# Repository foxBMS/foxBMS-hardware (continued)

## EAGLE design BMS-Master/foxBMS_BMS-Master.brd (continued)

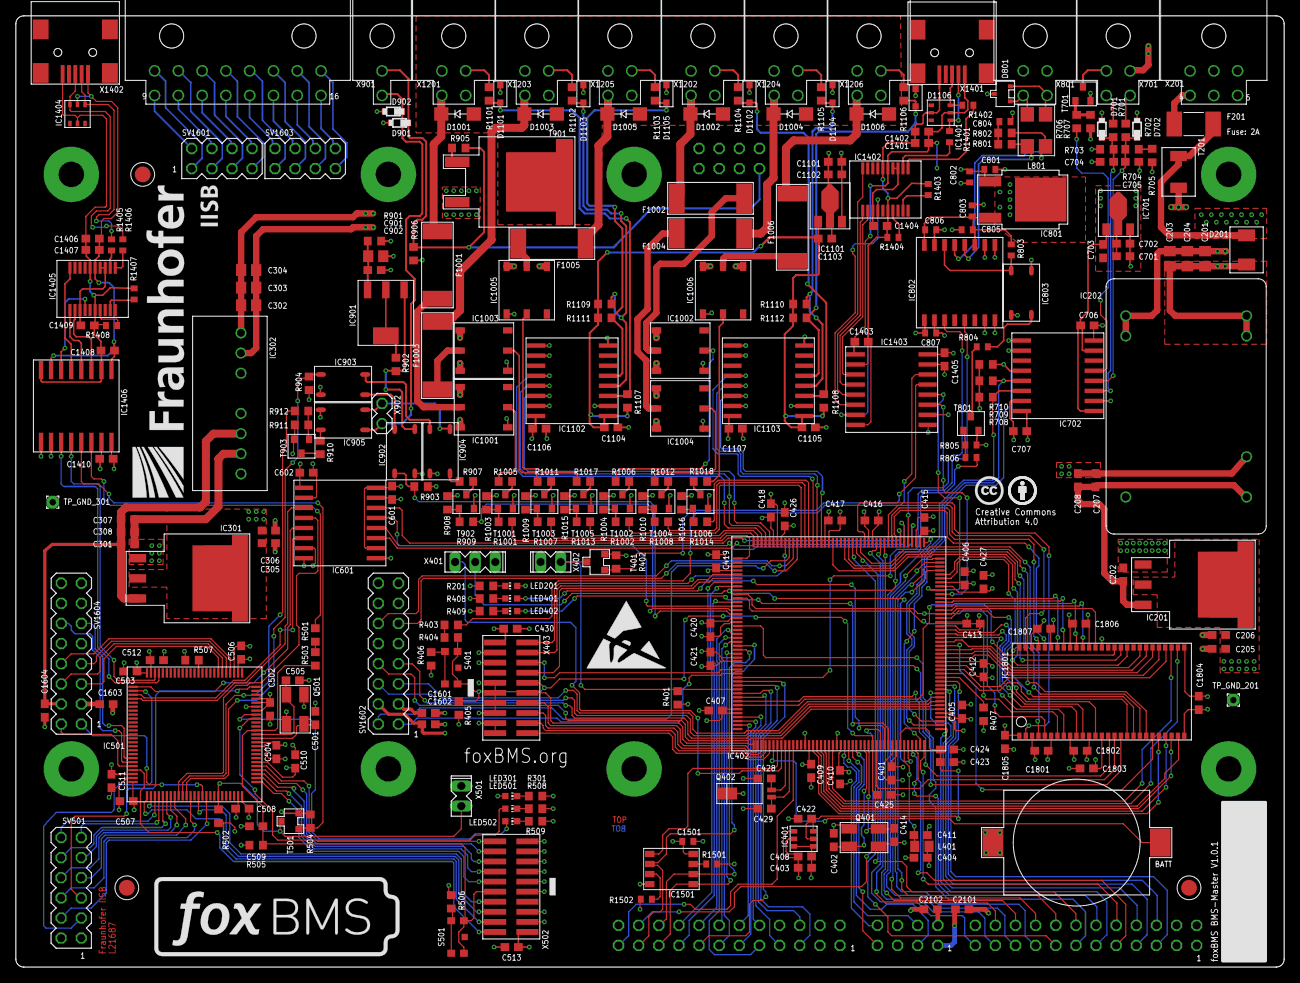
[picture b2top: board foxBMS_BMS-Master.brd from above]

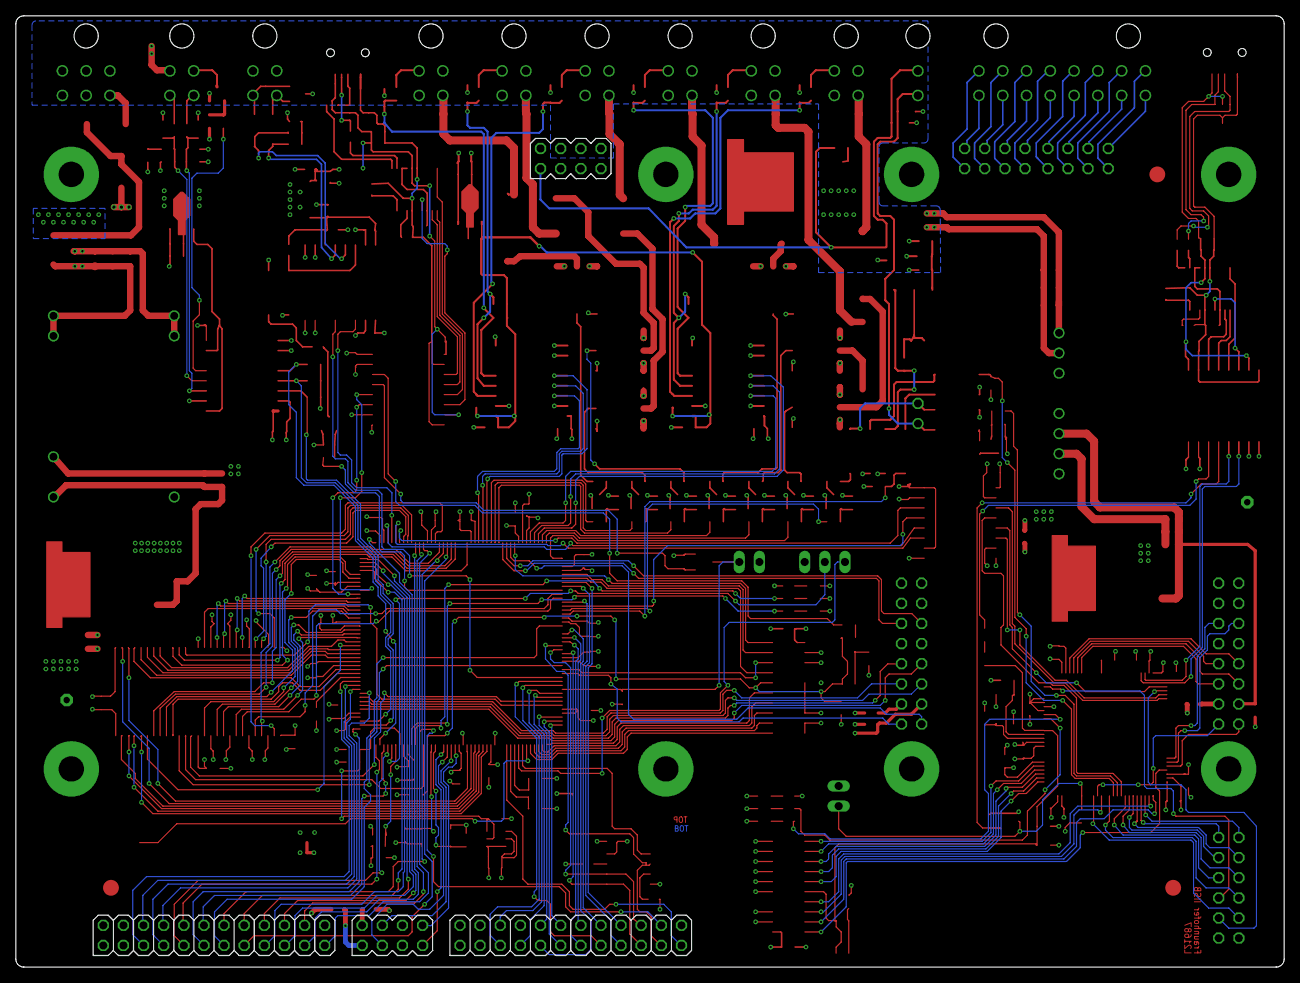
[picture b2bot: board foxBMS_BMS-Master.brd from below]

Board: 4 copper layers, 160.0 x 120.0 mm, 318 parts (4 on the bottom side), 331 nets.

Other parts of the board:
U$1, U$3, U$4: FIDUCIAL_1MM
U$2: ESD_10.00

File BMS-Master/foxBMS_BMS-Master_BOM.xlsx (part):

| Pos | Populate | Qty | Value | Device | Package | Parts | Description | Farnell | Digikey | Mouser
Resistor
 | 1 | yes | 9 | 0 | R-EU_R0603 | R0603 | R403 R406 R501 R506 R705 R1403 R1404 R1407 R1408 | RESISTOR, European symbol | 2059527
 | 2 | yes | 2 | 1.5k | R-EU_R0603 | R0603 | R701 R702 | RESISTOR, European symbol | 2303156
 | 3 | yes | 12 | 10 | R-EU_R0603 | R0603 | R706 R901 R905 R909 R912 R1001 R1002 R1007 R1008 R1013 R1014 R806 | RESISTOR, European symbol | 2302958
 | 4 | yes | 32 | 10k | R-EU_R0603 | R0603 | R401 R402 R405 R407 R502 R504 R505 R507 R707 R708 R709 R710 R903 R904 R908 R911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 | RESISTOR, European symbol | 2303192
 | 5 | yes | 1 | 120 | R-EU_R0603 | R0603 | R902 | RESISTOR, European symbol | 2303067
 | 6 | yes | 6 | 130 | R-EU_R0603 | R0603 | R201 R301 R408 R409 R508 R509 | RESISTOR, European symbol | 2059288
 | 7 | yes | 8 | 430 | R-EU_R0603 | R0603 | R907 R910 R1005 R1006 R1011 R1012 R1017 R1018 R804 | RESISTOR, European symbol | 2145386
 | 8 | yes | 1 | 330 | R-EU_R0603 | R0603 | R906 | RESISTOR, European symbol | 2145370
 | 9 | yes | 4 | 27 | R-EU_R0603 | R0603 | R1401 R1402 R1405 R1406 | RESISTOR, European symbol | 2145363
 | 10 | yes | 6 | 47 | R-EU_R0603 | R0603 | R1101 R1102 R1103 R1104 R1105 R1106 | RESISTOR, European symbol | 2145397
 | 11 | yes | 2 | 62 | R-EU_R0603 | R0603 | R801 R802 | RESISTOR, European symbol | 2303039
 | 12 | yes | 4 | 680 | R-EU_R0603 | R0603 | R404 R503 R703 R704 | RESISTOR, European symbol | 2303131
Capacitor
 | 13 | yes | 74 | 100n | C-EUC0603 | C0603 | C202 C206 C208 C301 C306 C308 C401 C404 C405 C406 C407 C408 C409 C410 C411 C412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 | CAPACITOR, European symbol | 1828890
 | 14 | yes | 4 | 100n 50V | C-EUC0604 | C0603 | C702 C802 C902 C1102 | CAPACITOR, European symbol | 2346967
 | 15 | yes | 8 | 18p | C-EUC0605 | C0603 | C402 C414 C428 C429 C501 C505 C704 C705 | CAPACITOR, European symbol | 2070403
 | 16 | yes | 6 | 1µ | C-EUC0606 | C0603 | C205 C207 C305 C307 C403 C423 | CAPACITOR, European symbol | 1907343
 | 17 | yes | 3 | 1µ 35V | C-EUC0607 | C0603 | C701 C801 C1101 | CAPACITOR, European symbol | 2346909
 | 18 | yes | 4 | 2.2µ | C-EUC0608 | C0603 | C426 C427 C511 C512 | CAPACITOR, European symbol | 2346961
 | 19 | yes | 7 | 2.2µ 50V | C-EUC0609 | C0805 | C201 C203 C204 C302 C303 C304 C901 | CAPACITOR, European symbol | 2346945
 | 20 | yes | 2 | 4.7µ | C-EUC0610 | C0603 | C1401 C1406 | CAPACITOR, European symbol | 2362098
L
 | 21 | yes | 1 |  | L0805 | 0805 | L401 |  | 2443249
 | 22 | yes | 1 |  | B82789N | B82789N | L801 |  |  |  | 871-B82789C513N2
LED
 | 23 | yes | 2 | Green | LEDCHIP-LED0603 | CHIP-LED0603 | LED402 LED502 | LED | 2099223
 | 24 | yes | 2 | Red | LEDCHIP-LED0603 | CHIP-LED0603 | LED401 LED501 | LED | 2099221
 | 25 | yes | 2 | Orange | LEDCHIP-LED0603 | CHIP-LED0603 | LED201 LED301 | LED | 2099222
XTAL
 | 26 | yes | 2 | 7B-8.000MAAJ-T | 7B-8.000MAAJ-T | MJ | Q401 Q501 | MJ Quarz, 5 x 3.2 x 1.0mm SMD | 2308726
 | 27 | yes | 1 |  | MS3V | MS3V-T1R | Q402 |  | 1539368
Transistor
 | 28 | yes | 2 | BSS84P | BSS84P | SOT23 | T401 T501 | #2245 | 1056526
 | 29 | yes | 1 | BUK964R8-60E | BUK964R8-60E | TO-263AB | T901 | #2797 N-Channel PowerTrench MOSFET 60V, 75A 10.5mOhm | 2254205
 | 30 | yes | 10 | IRLML0100TRPBF | IRLML0100TRPBF | SOT-23 | T701 T801 T902 T903 T1001 T1002 T1003 T1004 T1005 T1006 |  | 1783928
IC
 | 31 | yes | 1 | ADR3425 | ADR3425 | SOT23-6 | IC401 | Micropower, high accuracy, voltage references | 2377039
 | 32 | yes | 2 | ADUM3300 | ADUM3300 | SO-16W | IC1102 IC1103 | Triple-Channel Digital Isolators | 2409432
 | 33 | yes | 1 | ADUM3301 | ADUM3301 | SO-16W | IC702 | Triple-Channel Digital Isolators | 2462515
 | 34 | yes | 3 | ADUM3401 | ADUM3401 | SO16W | IC601 IC1403 IC1406 | Analog Devices Magnetkoppler 4-Kanal | 1274129
 | 35 | yes | 2 | FT231XS-R | FT231XS-R | IC_SMD_SSOP-20 | IC1402 IC1405 | FT231X?-* - FTDI | 2081328
 | 36 | yes | 1 | AT25128B-SSHL-T | AT25128B-SSHL-T | SO8 | IC1501 | SPI bus serial EEPROM | 2345601
 | 37 | yes | 1 | TJA1052IT/5Y | TJA1052IT/5Y | SO16W | IC802 |  | 2400552
Diode
 | 38 | yes | 1 | PESD1CAN | PESD1CAN | SOT-23_NEU | D801 | NXP PESD1CAN CAN bus ESD protection diode | 1510703
 | 39 | yes | 1 | STPS3L60U | STPS3L60U | SMB | D201 | Schottky Diode | 9907769
 | 40 | yes | 2 | MM3Z12VT1G | MM3Z12VT1G | SOD323 | D901 D902 | MM3Z_xVx_T1 Series Zener Diode | 1431191
 | 41 | yes | 6 | CDSOD323-T05 | CDSOD323-T05 | SOD323 | D1101 D1102 D1103 D1104 D1105 D1106 | TVS CDSOD323-T05 | 2341914
 | 42 | yes | 2 | MM3Z4V7ST1G | MM3Z4V7ST1G | SOD323 | D701 D702 | MM3Z_xVx_T1 Series Zener Diode | 2463512
 | 43 | no | 6 | GF1B | GF1B | SMA-DO214AC | D1001 D1002 D1003 D1004 D1005 D1006 | DIODE | 1467477
MCU
 | 44 | yes | 1 | STM32F429IIT6 | STM32F429IIT6 | LQFP176 | IC402 | ARM 32-bit Cortex™-M3 CPU |  | 497-14054-ND
 | 45 | yes | 1 | STM32F429VIT6 | STM32F429VGT6 | LQFP100 | IC501 | ARM 32-bit Cortex™-M3 CPU | 2393659
Regulator
 | 46 | yes | 1 | KA7805ERTF | KA7805ERTF | TO252 | IC801 | Positive VOLTAGE REGULATOR | 2102585
 | 47 | yes | 2 | UA78L05CPK | UA78L05CPK | SOT89 | IC701 IC1101 | POSITOIV-VOLTAGE REGULATORS | 2112604
 | 48 | yes | 2 | LM1085-3.3 | LM1085-3.3 | TO-263-3L | IC201 IC301 | National Semiconductor LM1085IS-5 3A Low Dropout Positive Regulators | 1469039
 | 49 | yes | 1 | LM317MSTT3 | LM317MSTT3 | SOT223 | IC901 | 500 mA Adjustable Output Positive Voltage Regulator | 1703412
Opto
 | 50 | yes | 6 | AQV252G2SX | AQV252G2SX | SOP06 | IC1001 IC1002 IC1003 IC1004 IC1005 IC1006 |  |  | 255-3594-1-ND
 | 51 | yes | 5 | CPC1008N | CPC1008N | SOP4 | IC803 IC902 IC903 IC904 IC905 | CLARE - Single-Pol, Normally Open 4-Pin SOP OptoMOS Relay, 150mA load current | 1653755
Misc
 | 52 | yes | 1 | SMTU 1225-1-LF | SMTU 1225-1-LF | CR1225_SMD | BATT | #2833 | 1216353
 | 53 | yes | 2 | MC32598 | MC32598 | Mini-USB AB | X1401 X1402 | MINI USB-B Conector | 1696539
 | 54 | yes | 2 | IP4220CZ6 | IP4220CZ6 | TSOP-6 | IC1401 IC1404 |  | 1506629
 | 55 | yes | 1 | IS42S16400J-7TLI | IS42S16400J-7TLI | TSOP-54 | IC1801 |  | 2253831
 | 56 | yes | 2 | KMR211G | KMR211G | KMR211G | S401 S501 | #228 |  | 401-1426-1-ND
 | 57 | yes | 6 | 630MA_UMT | 630MA_UMT | F_SMD_11,00MMX3,00MMX3,00MM_(UMT)_R_SCHURTER_REV01 | F1001 F1002 F1003 F1004 F1005 F1006 | UMT-Serie - Schurter Electronic Components |  | 486-2077-ND | 693-3403.0164.11
 | 58 | yes | 1 | 2A | Littelfuse 452 | NANO2 | F201 | 452 Serie Littelfuse | 2383284
 | 59 | yes | 1 | TISP4040H1BJR-S | TISP4040H1BJR-S | SMBJ | T201 | TVS Thyristor |  | TISP4040H1BJR-SCT-ND
Connector SMD
 | 60 | yes | 2 | FTS-110-01-L-DV | FTS-110-01-L-DV | FTS-110-01-L-DV | X403 X502 | SAMTEC connector, #537 | 1667733
Connector THD
 | 61 | yes | 1 | HEADER_POS16_43045-1599 | HEADER_POS16_43045-1600 | 43045-1600 | X1601 | Molex - Micro-Fit 3.0 Series connector, 3.00mm (0.118) pitch header, 16 positio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 | 9961380
 | 62 | yes | 1 | HEADER_POS2_43045-0199 | HEADER_POS2_43045-0200 | 43045-0200 | X901 | Molex - Micro-Fit 3.0 Series connector, 3.00mm (0.118) pitch header, 2 position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 | 1012251
 | 63 | yes | 8 | HEADER_POS4_43045-0400 | HEADER_POS4_43045-0401 | 43045-0400 | X701 X801 X1201 X1202 X1203 X1204 X1205 X1206 | Molex - Micro-Fit 3.0 Series connector, 3.00mm (0.118) pitch header, 4 position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 | 9733019
 | 64 | yes | 1 | HEADER_POS6_43045-0599 | HEADER_POS6_43045-0600 | 43045-0600 | X201 | Molex - Micro-Fit 3.0 Series connector, 3.00mm (0.118) pitch header, 6 position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 | 1012252
 | 65 | yes | 1 | MA03-0 | MA03-1 | MA03-1 | X401 | 3Pins | 2505045
 | 66 | yes | 1 |  |  |  | SV901 | 8 Header | 1668094
 | 67 | yes | 3 | MA04-1 | MA04-2 | MA04-2 | SV1601 SV1603 SV2101 | 8 Pins | 2025250
 | 68 | yes | 1 | MA06-1 | MA06-2 | MA06-2 | SV501 | 12 Pins | 2025252
 | 69 | yes | 2 | MA08-1 | MA08-2 | MA08-2 | SV1602 SV1604 | 16 Pins | 2025254
 | 70 | no | 1 | MA02-0 | MA02-0 | MA02-0 | X902 | 1 Pins | 2505044
 | 71 | yes | 2 | MA02-1 | MA02-1 | MA02-1 | X402 X501 | 2 Pins | 2505044
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
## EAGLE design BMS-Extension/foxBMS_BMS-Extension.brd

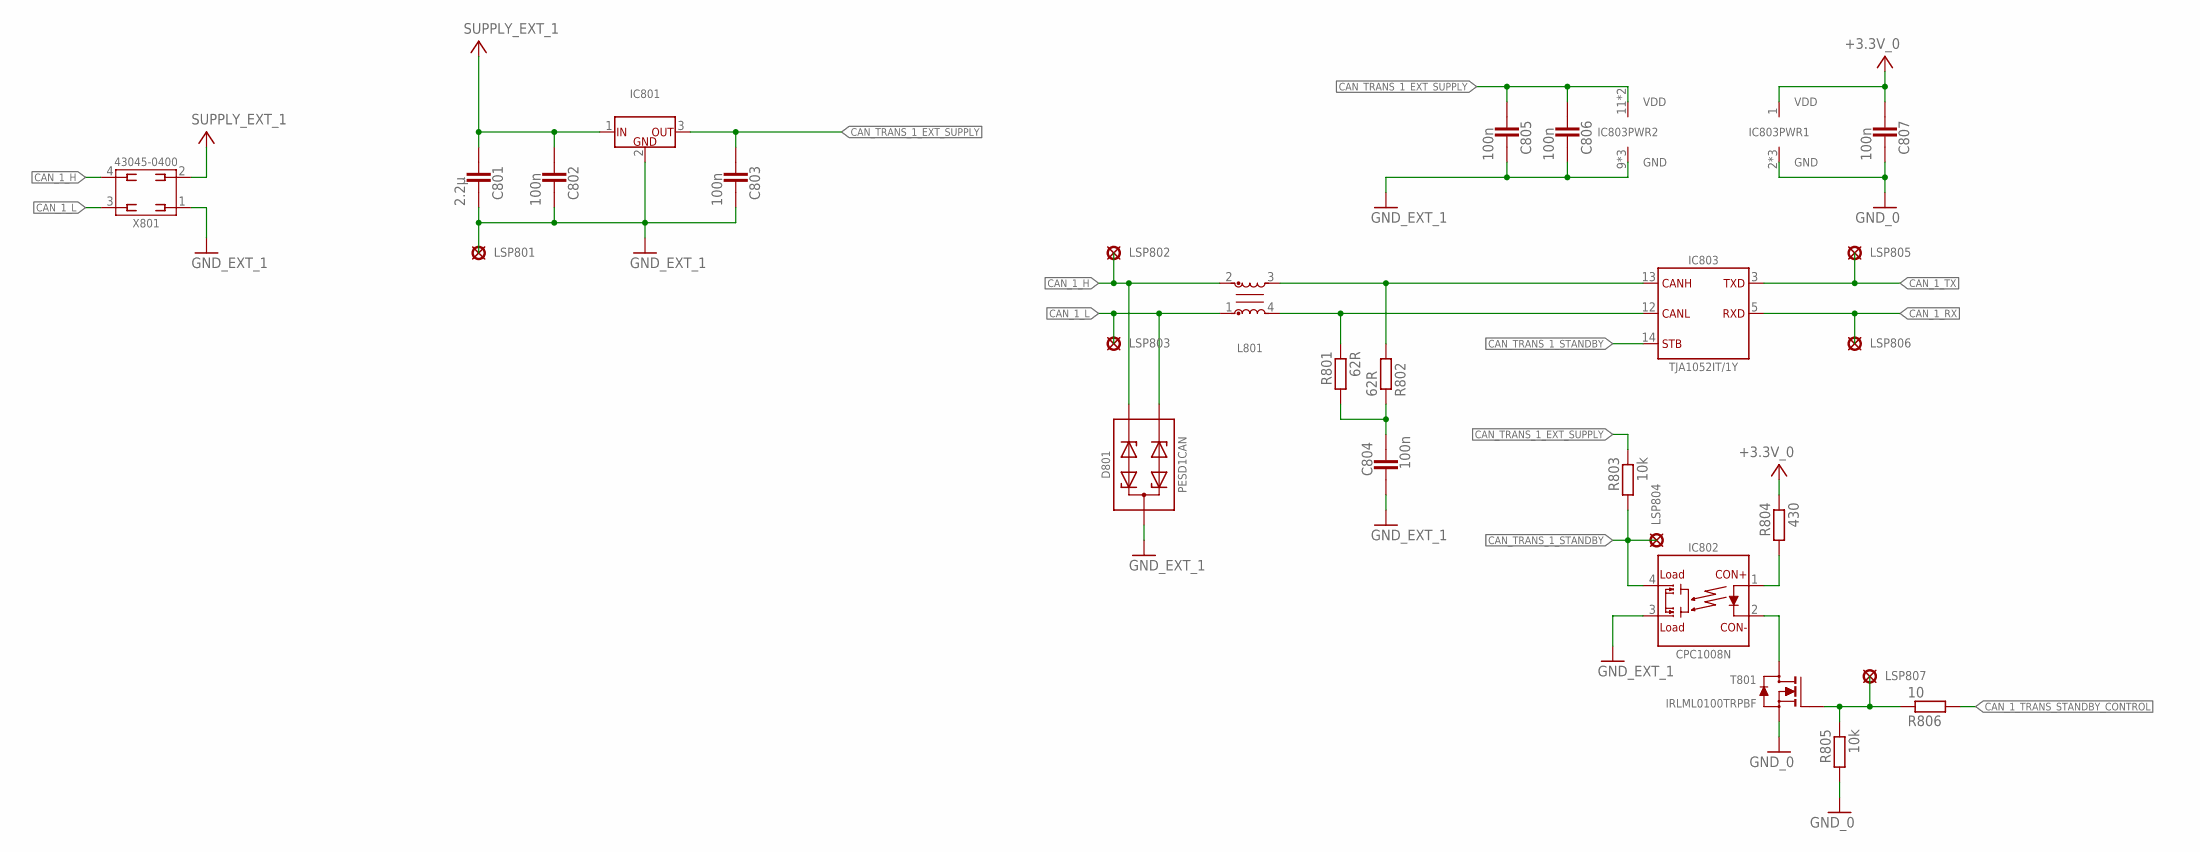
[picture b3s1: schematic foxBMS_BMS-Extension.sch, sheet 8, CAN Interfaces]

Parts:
C801: 2.2µ; 0603
C802, C803, C804, C805, C806, C807: 100n; 0603
D801: PESD1CAN; D_SMD_SOT23_(TO-236AB)_R_NXP_REV01
IC801: KA7805ERTF; IC_SMD_TO-252_(D-PAK)_R_FAIRCHILD_REV01
IC802: CPC1008N; K_SMD_SOP-4_R_IXYS_REV01
IC803: TJA1052IT/1Y; IC_SMD_SO16_(SOT162-1)_R_NXP_REV01
L801: B82789C0513N002; L_SMD_FILTER_HF_R_EPCOS_SIMDAD_1812_REV01
LSP801, LSP802, LSP803, LSP804, LSP805, LSP806, LSP807: PAD_2.0X1.5MM; PAD2.0X1.5MM
R801, R802: 62R; 0603
R803, R805: 10k; 0603
R804: 430; 0603
R806: 10; 0603
T801: IRLML0100TRPBF; V_SMD_SOT-23_(TO-236AB)_R_IR_REV01
X801: 43045-0400_MOLEX_4PIN; X_TH_MOLEX_43045-0400_R_REV01

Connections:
+3.3V_0: C807.2, IC803.1 (VDD), R804.1; also elsewhere on the board
CAN_1_H: D801.1, L801.2, LSP802.P$1, X801.4
CAN_1_L: D801.2, L801.1, LSP803.P$1, X801.3
CAN_1_RX: IC803.5 (RXD), LSP806.P$1; also elsewhere on the board
CAN_1_TRANS_STANDBY_CONTROL: R806.2; also elsewhere on the board
CAN_1_TX: IC803.3 (TXD), LSP805.P$1; also elsewhere on the board
CAN_L_INT1: IC803.12 (CANL), L801.4, R801.1
CAN_SPLIT1: C804.1, R801.2, R802.1
CAN_TRANS_1_EXT_SUPPLY: C803.2, C805.2, C806.2, IC801.3 (OUT), IC803.11 (VDD), IC803.16 (VDD), R803.1
CAN_TRANS_1_STANDBY: IC802.4, IC803.14 (STB), LSP804.P$1, R803.2
GND_0: C807.1, IC803.2 (GND), IC803.7 (GND), IC803.8 (GND), R805.2, T801.2 (S); also elsewhere on the board
GND_EXT_1: C801.1, C802.1, C803.1, C804.2, C805.1, C806.1, D801.3, IC801.2 (GND), IC802.3, IC803.9 (GND), IC803.10 (GND), IC803.15 (GND), LSP801.P$1, X801.1
unnamed: IC803.13 (CANH), L801.3, R802.2
unnamed: IC802.2 (CON-), T801.3 (D)
unnamed: IC802.1 (CON+), R804.2
unnamed: LSP807.P$1, R805.1, R806.1, T801.1 (G)
SUPPLY_EXT_1: C801.2, C802.2, IC801.1 (IN), X801.2

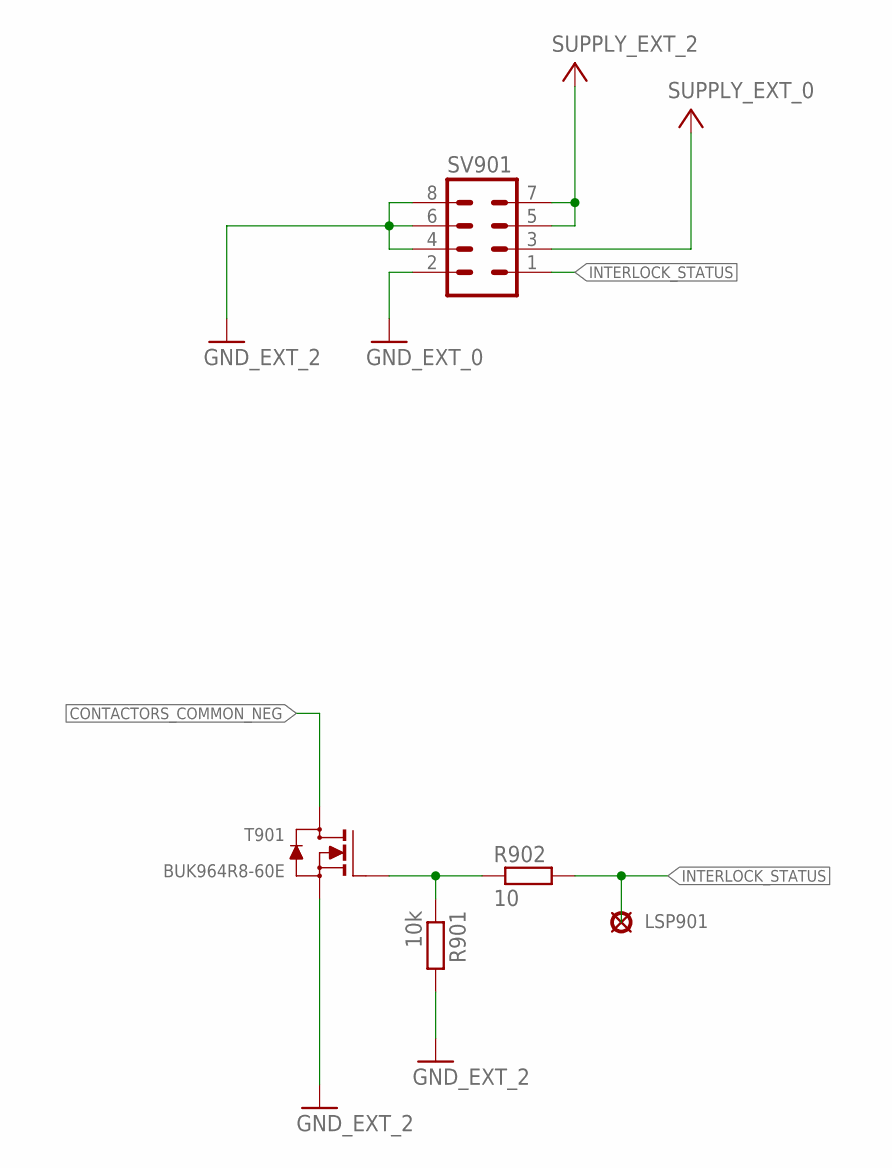
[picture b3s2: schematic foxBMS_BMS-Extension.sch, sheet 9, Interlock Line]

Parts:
LSP901: PAD_2.0X1.5MM; PAD2.0X1.5MM
R901: 10k; 0603
R902: 10; 0603
SV901: MA04-2
T901: BUK964R8-60E; V_SMD_TO-263_(D²PAK)_R_NXP_REV01

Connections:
CONTACTORS_COMMON_NEG: T901.2 (D); also elsewhere on the board
GND_EXT_0: SV901.2; also elsewhere on the board
GND_EXT_2: R901.2, SV901.4, SV901.6, SV901.8, T901.3 (S); also elsewhere on the board
INTERLOCK_STATUS: LSP901.P$1, R902.2, SV901.1
unnamed: R901.1, R902.1, T901.1 (G)
SUPPLY_EXT_0: SV901.3; also elsewhere on the board
SUPPLY_EXT_2: SV901.5, SV901.7; also elsewhere on the board

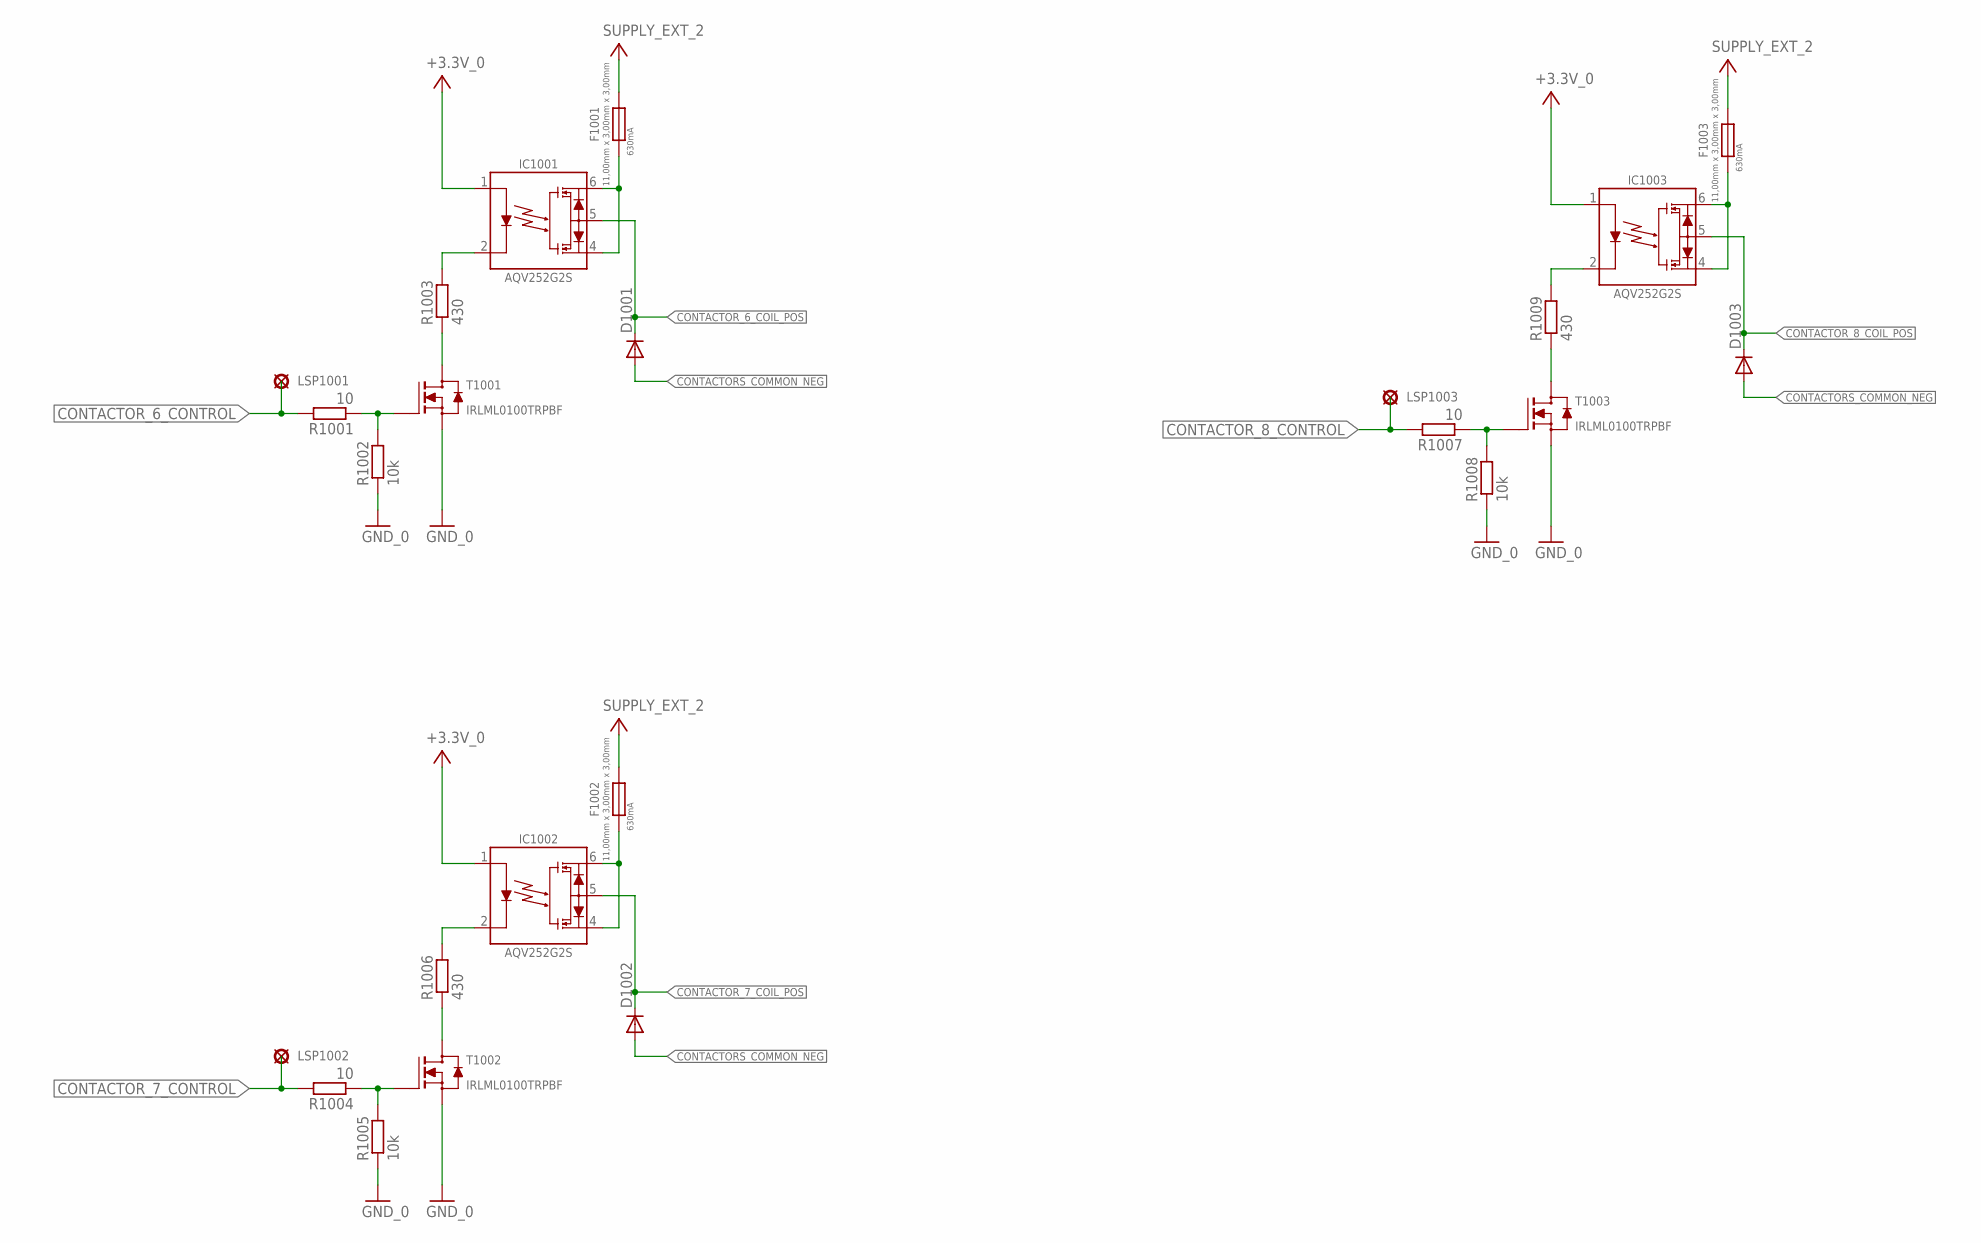
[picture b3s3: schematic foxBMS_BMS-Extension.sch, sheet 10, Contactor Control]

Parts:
D1001, D1002, D1003: DIODE-DO214BA; DO214BA
F1001, F1002, F1003: 630MA_UMT; F_SMD_11,00MMX3,00MMX3,00MM_(UMT)_R_SCHURTER_REV01
IC1001, IC1002, IC1003: AQV252G2S; K_SMD_SOP-6_R_PANASONIC_REV01
LSP1001, LSP1002, LSP1003: PAD_2.0X1.5MM; PAD2.0X1.5MM
R1001, R1004, R1007: 10; 0603
R1002, R1005, R1008: 10k; 0603
R1003, R1006, R1009: 430; 0603
T1001, T1002, T1003: IRLML0100TRPBF; V_SMD_SOT-23_(TO-236AB)_R_IR_REV01

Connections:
+3.3V_0: IC1001.1, IC1002.1, IC1003.1; also elsewhere on the board
CONTACTORS_COMMON_NEG: D1001.A, D1002.A, D1003.A; also elsewhere on the board
CONTACTOR_6_COIL_POS: D1001.C, IC1001.5; also elsewhere on the board
CONTACTOR_6_CONTROL: LSP1001.P$1, R1001.2; also elsewhere on the board
CONTACTOR_7_COIL_POS: D1002.C, IC1002.5; also elsewhere on the board
CONTACTOR_7_CONTROL: LSP1002.P$1, R1004.2; also elsewhere on the board
CONTACTOR_8_COIL_POS: D1003.C, IC1003.5; also elsewhere on the board
CONTACTOR_8_CONTROL: LSP1003.P$1, R1007.2; also elsewhere on the board
GND_0: R1002.1, R1005.1, R1008.1, T1001.2 (S), T1002.2 (S), T1003.2 (S); also elsewhere on the board
unnamed: R1003.1, T1001.3 (D)
unnamed: R1006.1, T1002.3 (D)
unnamed: R1009.1, T1003.3 (D)
unnamed: F1001.1, IC1001.4, IC1001.6
unnamed: F1002.1, IC1002.4, IC1002.6
unnamed: F1003.1, IC1003.4, IC1003.6
unnamed: IC1001.2, R1003.2
unnamed: R1001.1, R1002.2, T1001.1 (G)
unnamed: IC1002.2, R1006.2
unnamed: R1004.1, R1005.2, T1002.1 (G)
unnamed: IC1003.2, R1009.2
unnamed: R1007.1, R1008.2, T1003.1 (G)
SUPPLY_EXT_2: F1001.2, F1002.2, F1003.2; also elsewhere on the board

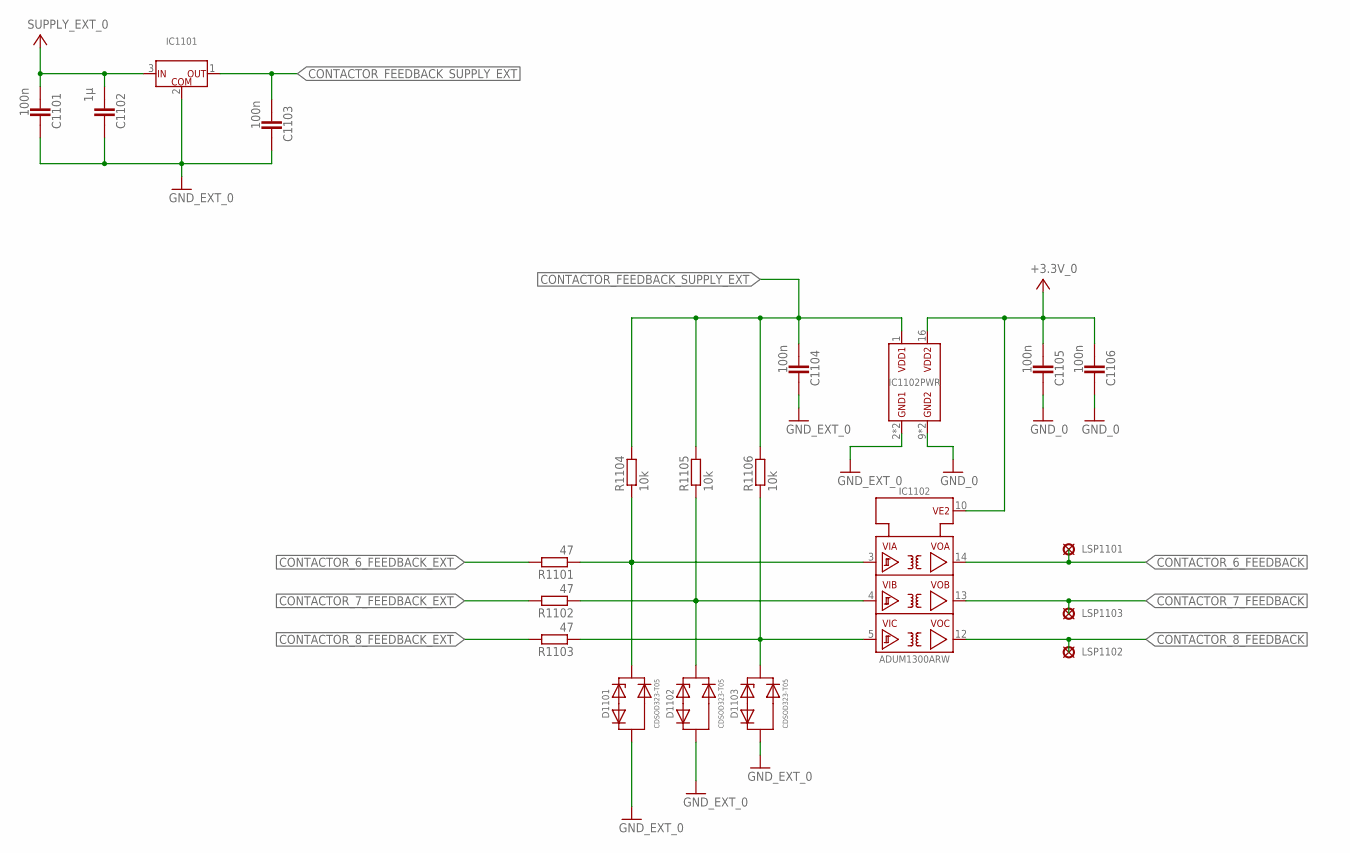
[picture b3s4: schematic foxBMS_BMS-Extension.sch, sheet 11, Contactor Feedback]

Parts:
C1101, C1103, C1104, C1105, C1106: 100n; 0603
C1102: 1µ; 0603
D1101, D1102, D1103: CDSOD323-T05; D_SMD_SOD323_(SC-76)_R_BOURNS_REV01
IC1101: UA78L05ACPK; IC_SMD_SOT-89_(SC-62/TO-243)_(R-PSSO-F3)_R_TI_REV01
IC1102: ADUM1300ARW; IC_SMD_SOIC-16_(JEDEC_MS-013-AA)_R_ANALOG_REV01
LSP1101, LSP1102, LSP1103: PAD_2.0X1.5MM; PAD2.0X1.5MM
R1101, R1102, R1103: 47; 0603
R1104, R1105, R1106: 10k; 0603

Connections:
+3.3V_0: C1105.1, C1106.1, IC1102.10 (VE2), IC1102.16 (VDD2); also elsewhere on the board
CONTACTOR_6_FEEDBACK: IC1102.14 (VOA), LSP1101.P$1; also elsewhere on the board
CONTACTOR_6_FEEDBACK_EXT: R1101.2; also elsewhere on the board
CONTACTOR_7_FEEDBACK: IC1102.13 (VOB), LSP1103.P$1; also elsewhere on the board
CONTACTOR_7_FEEDBACK_EXT: R1102.2; also elsewhere on the board
CONTACTOR_8_FEEDBACK: IC1102.12 (VOC), LSP1102.P$1; also elsewhere on the board
CONTACTOR_8_FEEDBACK_EXT: R1103.2; also elsewhere on the board
CONTACTOR_FEEDBACK_SUPPLY_EXT: C1103.1, C1104.1, IC1101.1 (OUT), IC1102.1 (VDD1), R1104.2, R1105.2, R1106.2
GND_0: C1105.2, C1106.2, IC1102.9 (GND2), IC1102.15 (GND2); also elsewhere on the board
GND_EXT_0: C1101.2, C1102.2, C1103.2, C1104.2, D1101.A, D1102.A, D1103.A, IC1101.2 (COM), IC1102.2 (GND1), IC1102.8 (GND1); also elsewhere on the board
unnamed: D1101.C, IC1102.3 (VIA), R1101.1, R1104.1
unnamed: D1102.C, IC1102.4 (VIB), R1102.1, R1105.1
unnamed: D1103.C, IC1102.5 (VIC), R1103.1, R1106.1
SUPPLY_EXT_0: C1101.1, C1102.1, IC1101.3 (IN); also elsewhere on the board

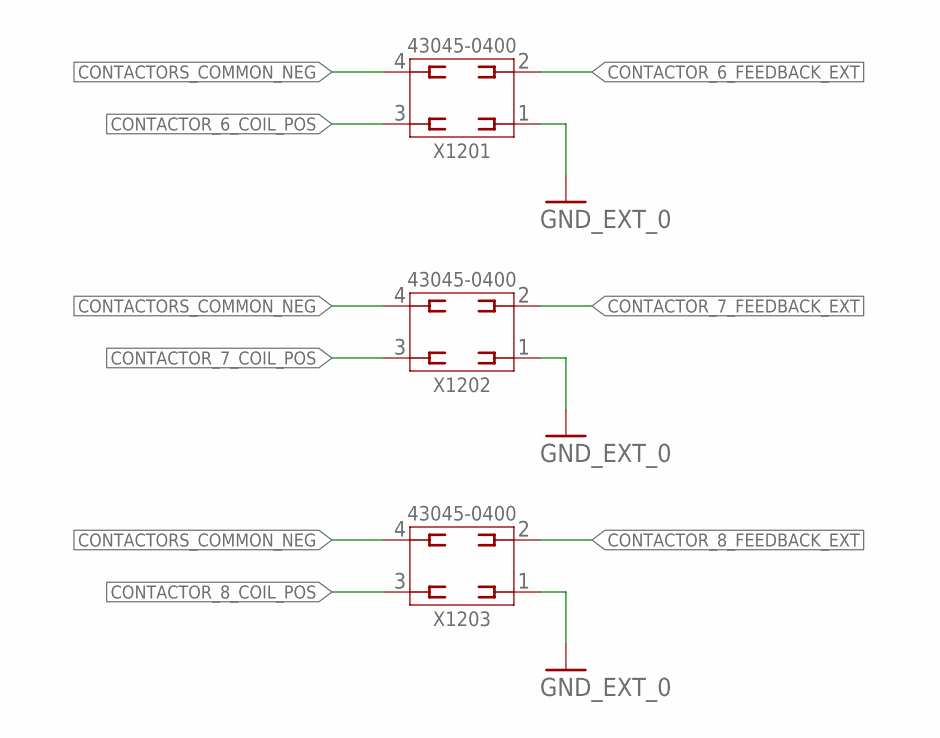
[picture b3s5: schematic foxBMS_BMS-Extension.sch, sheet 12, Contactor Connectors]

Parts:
X1201, X1202, X1203: 43045-0400_MOLEX_4PIN; X_TH_MOLEX_43045-0400_R_REV01

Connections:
CONTACTORS_COMMON_NEG: X1201.4, X1202.4, X1203.4; also elsewhere on the board
CONTACTOR_6_COIL_POS: X1201.3; also elsewhere on the board
CONTACTOR_6_FEEDBACK_EXT: X1201.2; also elsewhere on the board
CONTACTOR_7_COIL_POS: X1202.3; also elsewhere on the board
CONTACTOR_7_FEEDBACK_EXT: X1202.2; also elsewhere on the board
CONTACTOR_8_COIL_POS: X1203.3; also elsewhere on the board
CONTACTOR_8_FEEDBACK_EXT: X1203.2; also elsewhere on the board
GND_EXT_0: X1201.1, X1202.1, X1203.1; also elsewhere on the board

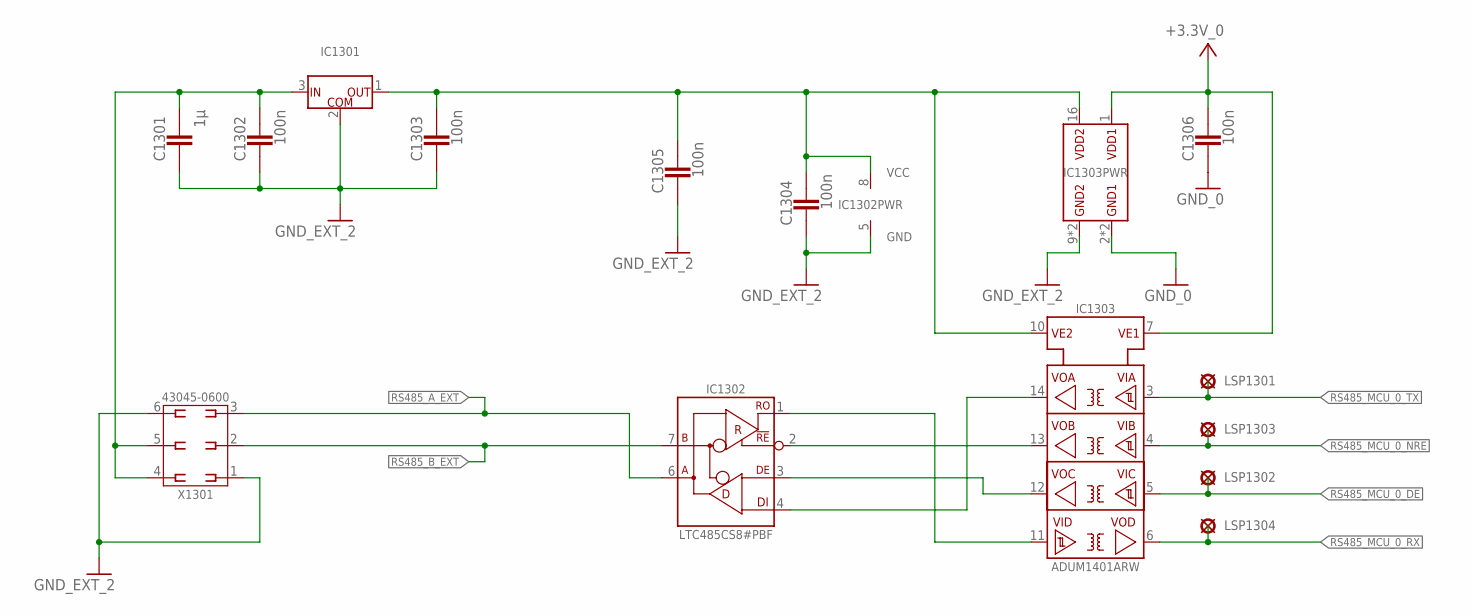
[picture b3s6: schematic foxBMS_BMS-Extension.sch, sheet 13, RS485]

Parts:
C1301: 1µ; 0603
C1302, C1303, C1304, C1305, C1306: 100n; 0603
IC1301: UA78L05ACPK; IC_SMD_SOT-89_(SC-62/TO-243)_(R-PSSO-F3)_R_TI_REV01
IC1302: LTC485CS8#PBF; IC_SMD_SOIC-8_(S8_REV_G)_R_LINEAR_REV01
IC1303: ADUM1401ARW; IC_SMD_SOIC-16_(JEDEC_MS-013-AA)_R_ANALOG_REV01
LSP1301, LSP1302, LSP1303, LSP1304: PAD_2.0X1.5MM; PAD2.0X1.5MM
X1301: 43045-0600_MOLEX_6PIN; X_TH_MOLEX_43045-0600_R_REV01

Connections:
+3.3V_0: C1306.1, IC1303.1 (VDD1), IC1303.7 (VE1); also elsewhere on the board
GND_0: C1306.2, IC1303.2 (GND1), IC1303.8 (GND1); also elsewhere on the board
GND_EXT_2: C1301.2, C1302.2, C1303.2, C1304.2, C1305.2, IC1301.2 (COM), IC1302.5 (GND), IC1303.9 (GND2), IC1303.15 (GND2), X1301.1, X1301.6; also elsewhere on the board
unnamed: C1301.1, C1302.1, IC1301.3 (IN), X1301.4, X1301.5
unnamed: IC1302.1 (RO), IC1303.11 (VID)
unnamed: IC1302.2 (!RE), IC1303.13 (VOB)
unnamed: IC1302.3 (DE), IC1303.12 (VOC)
unnamed: IC1302.4 (DI), IC1303.14 (VOA)
unnamed: C1303.1, C1304.1, C1305.1, IC1301.1 (OUT), IC1302.8 (VCC), IC1303.10 (VE2), IC1303.16 (VDD2)
RS485_A_EXT: IC1302.6 (A), X1301.3
RS485_B_EXT: IC1302.7 (B), X1301.2
RS485_MCU_0_DE: IC1303.5 (VIC), LSP1302.P$1; also elsewhere on the board
RS485_MCU_0_NRE: IC1303.4 (VIB), LSP1303.P$1; also elsewhere on the board
RS485_MCU_0_RX: IC1303.6 (VOD), LSP1304.P$1; also elsewhere on the board
RS485_MCU_0_TX: IC1303.3 (VIA), LSP1301.P$1; also elsewhere on the board

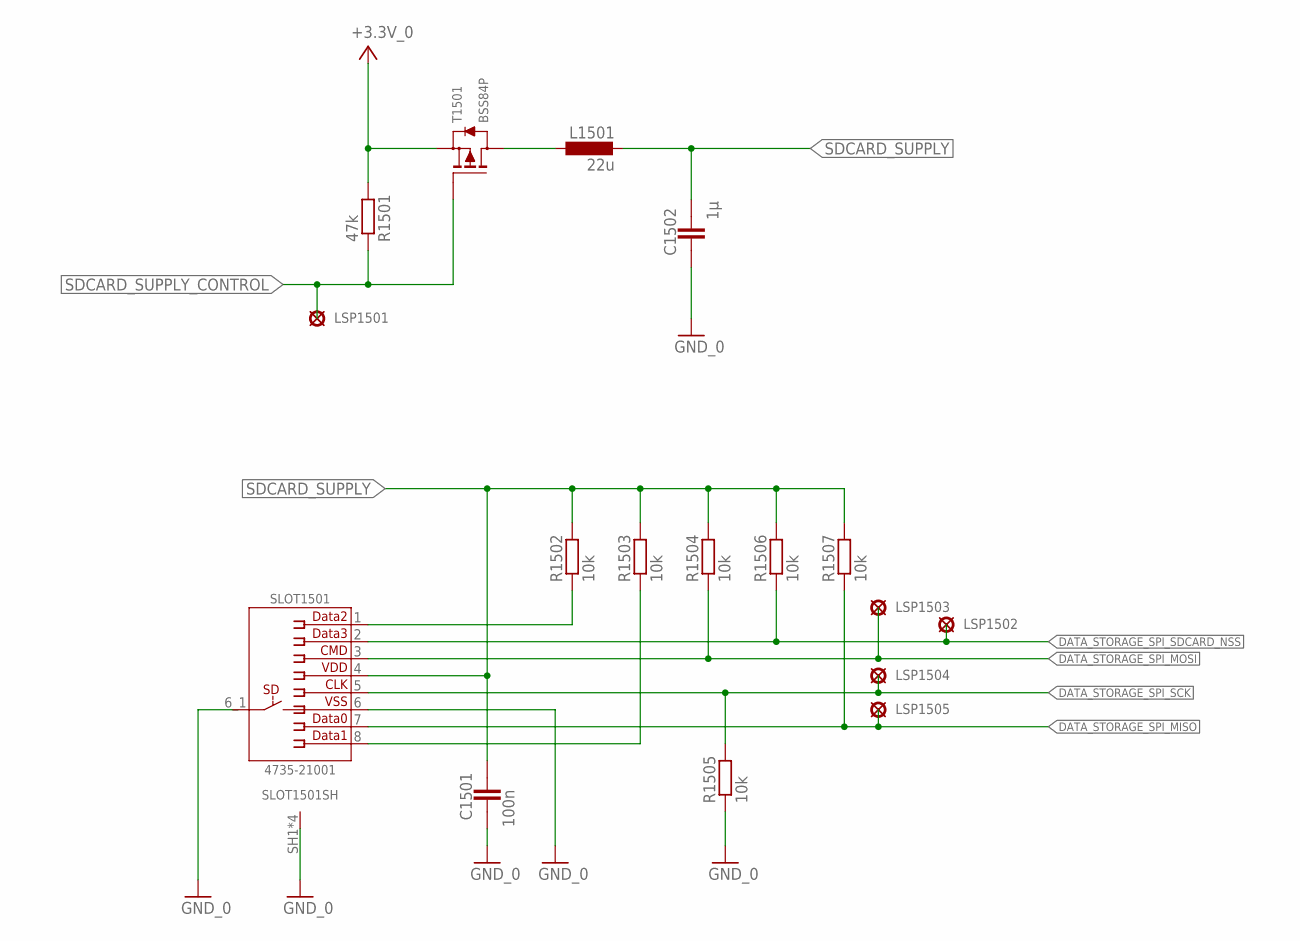
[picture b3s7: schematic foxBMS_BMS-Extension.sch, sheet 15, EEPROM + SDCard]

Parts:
C1501: 100n; 0603
C1502: 1µ; 0603
L1501: 22u; 0805
LSP1501, LSP1502, LSP1503, LSP1504, LSP1505: PAD_2.0X1.5MM; PAD2.0X1.5MM
R1501: 47k; 0603
R1502, R1503, R1504, R1505, R1506, R1507: 10k; 0603
SLOT1501: MICRO_SD; X_SMD_MICRO-SD-4735-21001_R_MOLEX_REV01
T1501: BSS84P; V_SMD_SOT23_(TO-236AB)_R_INFINEON_REV01

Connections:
+3.3V_0: R1501.2, T1501.2 (S); also elsewhere on the board
DATA_STORAGE_SPI_MISO: LSP1505.P$1, R1507.1, SLOT1501.7; also elsewhere on the board
DATA_STORAGE_SPI_MOSI: LSP1503.P$1, R1504.1, SLOT1501.3; also elsewhere on the board
DATA_STORAGE_SPI_SCK: LSP1504.P$1, R1505.2, SLOT1501.5; also elsewhere on the board
DATA_STORAGE_SPI_SDCARD_NSS: LSP1502.P$1, R1506.1, SLOT1501.2; also elsewhere on the board
GND_0: C1501.1, C1502.2, R1505.1, SLOT1501.6, SLOT1501.6_1 (9), SLOT1501.SH1 (SH), SLOT1501.SH2 (SH), SLOT1501.SH3 (SH), SLOT1501.SH5 (SH); also elsewhere on the board
unnamed: L1501.2, T1501.3 (D)
unnamed: R1502.1, SLOT1501.1
unnamed: R1503.1, SLOT1501.8
SDCARD_SUPPLY: C1501.2, C1502.1, L1501.1, R1502.2, R1503.2, R1504.2, R1506.2, R1507.2, SLOT1501.4
SDCARD_SUPPLY_CONTROL: LSP1501.P$1, R1501.1, T1501.1 (G); also elsewhere on the board
